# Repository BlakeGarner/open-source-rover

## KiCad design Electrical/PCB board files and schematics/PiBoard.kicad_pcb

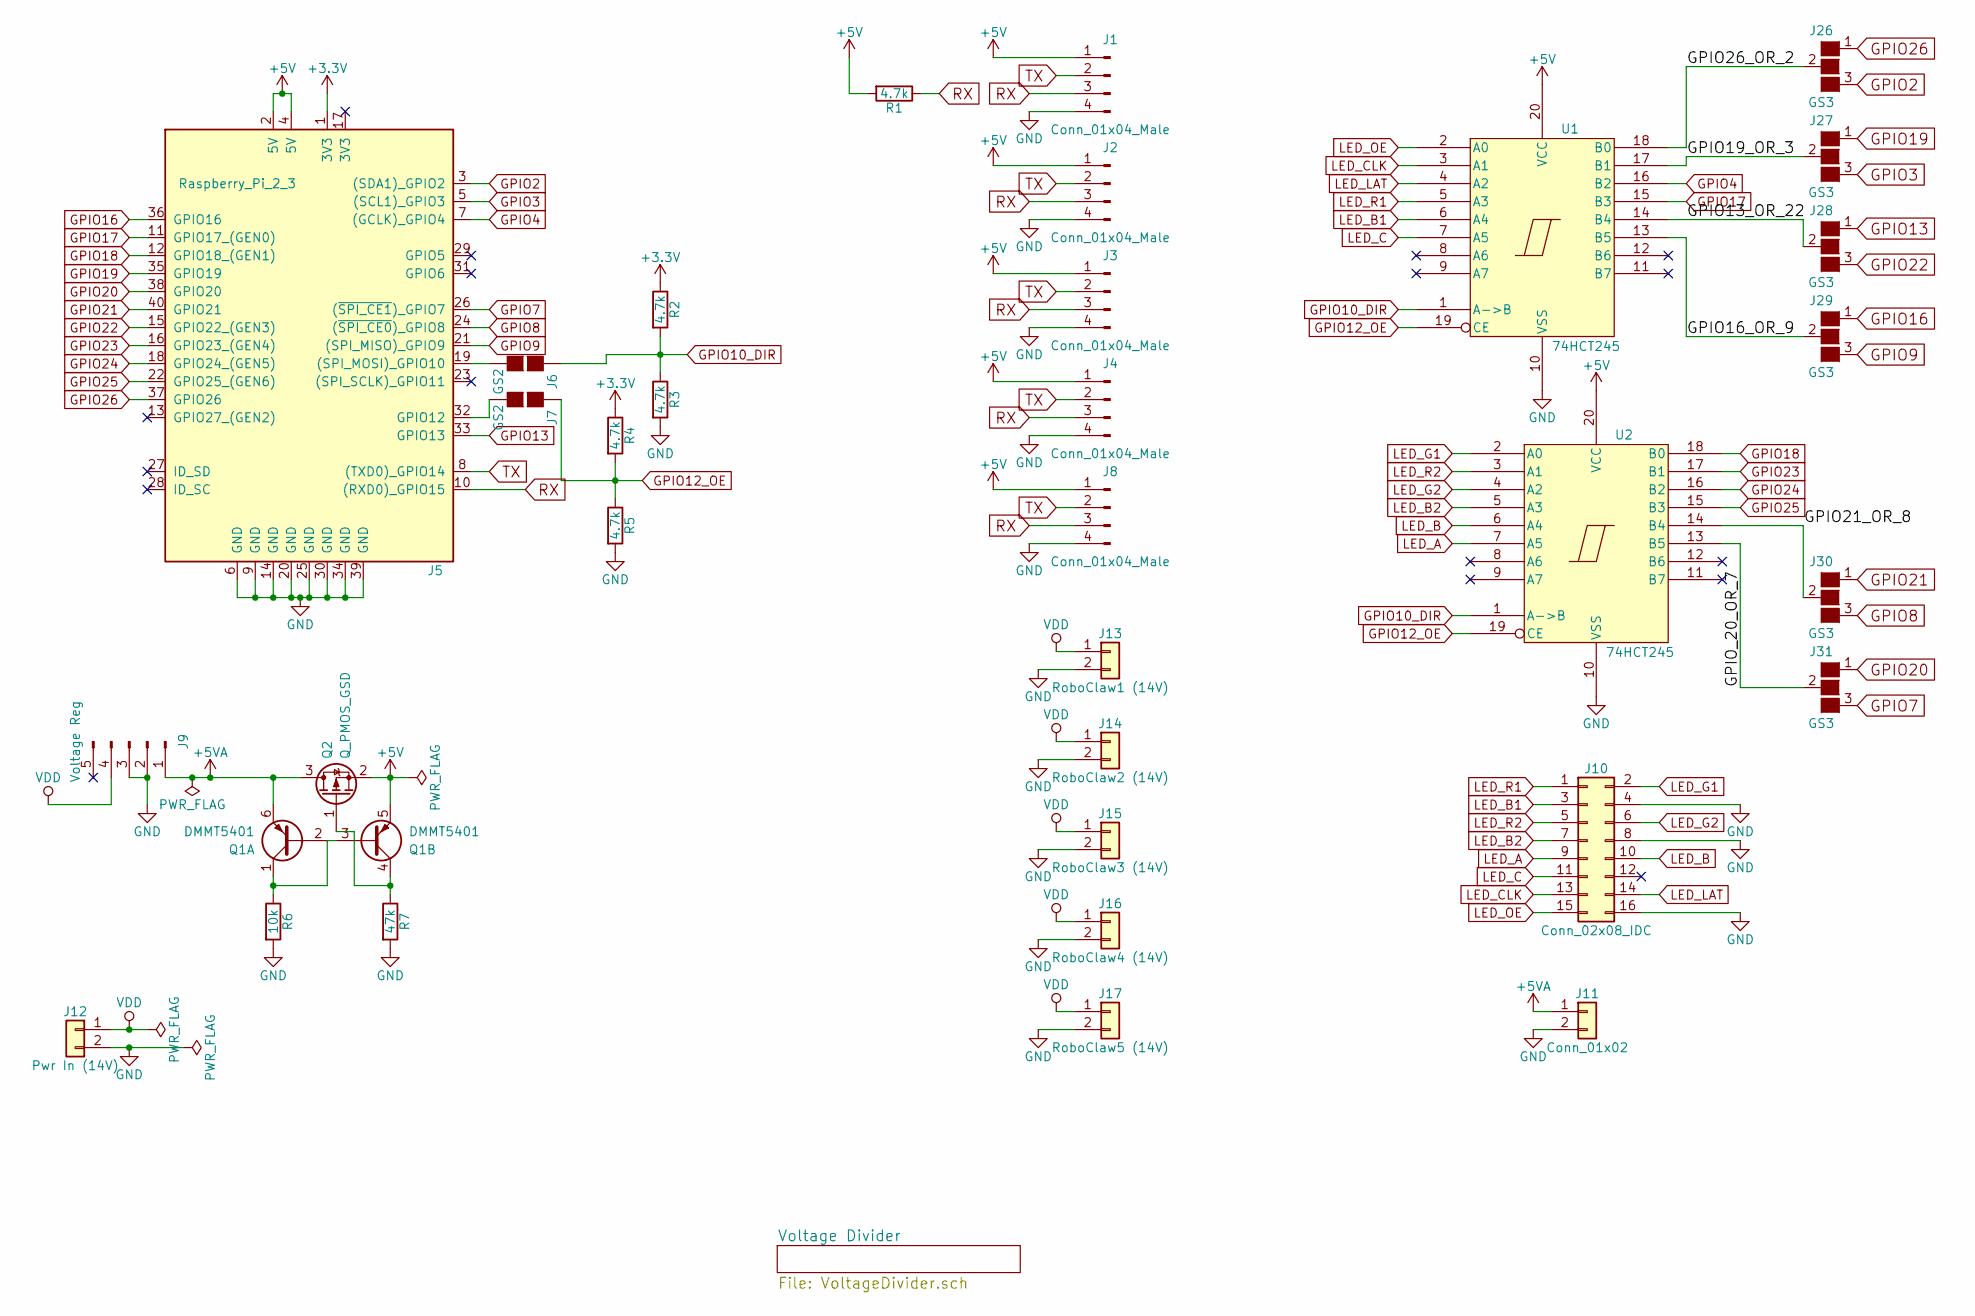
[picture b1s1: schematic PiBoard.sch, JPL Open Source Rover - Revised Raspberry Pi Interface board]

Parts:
J1, J2, J3, J4, J8: Conn_01x04_Male; Pin_Header_Straight_1x04_Pitch2.54mm
J5: Raspberry_Pi_2_3; Socket_Strip_Straight_Raspberry_Pi_2_3
J6, J7: GS2
J9: Voltage Reg; Pin_Header_Straight_1x05_Pitch2.54mm
J10: Conn_02x08_IDC; Multicomp_MC9A12-1634_2x08x2.54mm_Straight
J11: Conn_01x02; PhoenixContact_GMSTBVA-G_02x7.62mm_Vertical
J12: Pwr In (14V); PhoenixContact_GMSTBVA-G_02x7.62mm_Vertical
J13: RoboClaw1 (14V); TerminalBlock_bornier-2_P5.08mm
J14: RoboClaw2 (14V); TerminalBlock_bornier-2_P5.08mm
J15: RoboClaw3 (14V); TerminalBlock_bornier-2_P5.08mm
J16: RoboClaw4 (14V); TerminalBlock_bornier-2_P5.08mm
J17: RoboClaw5 (14V); TerminalBlock_bornier-2_P5.08mm
J26, J27, J28, J29, J30, J31: GS3
Q1: DMMT5401; SOT-23-6; MPN DMMT5401-7-F; Digikey PN DMMT5401-FDICT-ND
Q2: Q_PMOS_GSD; SOT-23; MPN DMG2305UX-13; Digikey PN DMG2305UX-13DICT-ND
R1, R2, R3, R4, R5: 4.7k; R_0805
R6: 10k; R_0805
R7: 47k; R_0805
U1, U2: 74HCT245; TSSOP-20_4.4x6.5mm_Pitch0.65mm

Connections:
+3V3: J5.1 (3V3), R2.1, R4.1
+5V: J1.1, J2.1, J3.1, J4.1, J5.2 (5V), J5.4 (5V), J8.1, Q1.5 (E2), Q2.2 (S), R1.2, U1.20 (VCC), U2.20 (VCC)
+5VA: J9.1, J11.1, Q1.6 (E1), Q2.3 (D)
/GPIO13_OR_22: J28.2 (G2), U1.14 (B4)
/GPIO16_OR_9: J29.2 (G2), U1.13 (B5)
/GPIO19_OR_3: J27.2 (G2), U1.17 (B1)
/GPIO21_OR_8: J30.2 (G2), U2.14 (B4)
/GPIO26_OR_2: J26.2 (G2), U1.18 (B0)
/GPIO_20_OR_7: J31.2 (G2), U2.13 (B5)
GND: J1.4, J2.4, J3.4, J4.4, J5.6 (GND), J5.9 (GND), J5.14 (GND), J5.20 (GND), J5.25 (GND), J5.30 (GND), J5.34 (GND), J5.39 (GND), J8.4, J9.2, J9.3, J10.4, J10.8, J10.16, J11.2, J12.2, J13.2, J14.2, J15.2, J16.2, J17.2, R3.2, R5.2, R6.2, R7.2, U1.10 (VSS), U2.10 (VSS)
GPIO2: J5.3 ((SDA1)_GPIO2), J26.3 (G3)
GPIO3: J5.5 ((SCL1)_GPIO3), J27.3 (G3)
GPIO4: J5.7 ((GCLK)_GPIO4), U1.16 (B2)
GPIO7: J5.26 ((~SPI_CE1~)_GPIO7), J31.3 (G3)
GPIO8: J5.24 ((~SPI_CE0~)_GPIO8), J30.3 (G3)
GPIO9: J5.21 ((SPI_MISO)_GPIO9), J29.3 (G3)
GPIO10_DIR: J6.1 (G1), R2.2, R3.1, U1.1 (A->B), U2.1 (A->B)
GPIO12_OE: J7.1 (G1), R4.2, R5.1, U1.19 (CE), U2.19 (CE)
GPIO13: J5.33 (GPIO13), J28.1 (G1)
GPIO16: J5.36 (GPIO16), J29.1 (G1)
GPIO17: J5.11 (GPIO17_(GEN0)), U1.15 (B3)
GPIO18: J5.12 (GPIO18_(GEN1)), U2.18 (B0)
GPIO19: J5.35 (GPIO19), J27.1 (G1)
GPIO20: J5.38 (GPIO20), J31.1 (G1)
GPIO21: J5.40 (GPIO21), J30.1 (G1)
GPIO22: J5.15 (GPIO22_(GEN3)), J28.3 (G3)
GPIO23: J5.16 (GPIO23_(GEN4)), U2.17 (B1)
GPIO24: J5.18 (GPIO24_(GEN5)), U2.16 (B2)
GPIO25: J5.22 (GPIO25_(GEN6)), U2.15 (B3)
GPIO26: J5.37 (GPIO26), J26.1 (G1)
LED_A: J10.9, U2.7 (A5)
LED_B: J10.10, U2.6 (A4)
LED_B1: J10.3, U1.6 (A4)
LED_B2: J10.7, U2.5 (A3)
LED_C: J10.11, U1.7 (A5)
LED_CLK: J10.13, U1.3 (A1)
LED_G1: J10.2, U2.2 (A0)
LED_G2: J10.6, U2.4 (A2)
LED_LAT: J10.14, U1.4 (A2)
LED_OE: J10.15, U1.2 (A0)
LED_R1: J10.1, U1.5 (A3)
LED_R2: J10.5, U2.3 (A1)
unnamed: J5.19 ((SPI_MOSI)_GPIO10), J6.2 (G2)
unnamed: J5.32 (GPIO12), J7.2 (G2)
unnamed: Q1.1 (C1), Q1.2 (B1), Q1.3 (B2), R6.1
unnamed: Q1.4 (C2), Q2.1 (G), R7.1
RX: J1.3, J2.3, J3.3, J4.3, J5.10 ((RXD0)_GPIO15), J8.3, R1.1
TX: J1.2, J2.2, J3.2, J4.2, J5.8 ((TXD0)_GPIO14), J8.2
VDD: J9.4, J12.1, J13.1, J14.1, J15.1, J16.1, J17.1

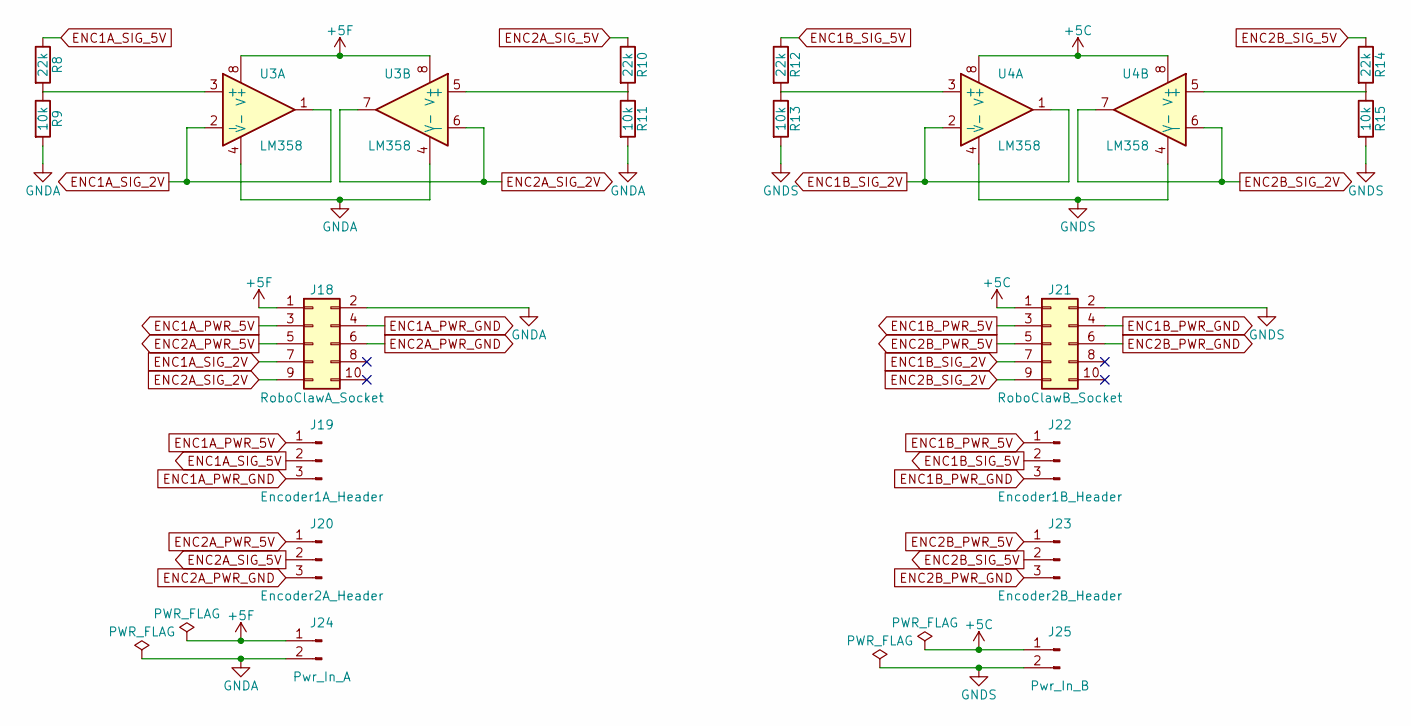
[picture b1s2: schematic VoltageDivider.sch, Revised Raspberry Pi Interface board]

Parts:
J18: RoboClawA_Socket; Pin_Header_Straight_2x05_Pitch2.54mm
J19: Encoder1A_Header; Pin_Header_Straight_1x03_Pitch2.54mm
J20: Encoder2A_Header; Pin_Header_Straight_1x03_Pitch2.54mm
J21: RoboClawB_Socket; Pin_Header_Straight_2x05_Pitch2.54mm
J22: Encoder1B_Header; Pin_Header_Straight_1x03_Pitch2.54mm
J23: Encoder2B_Header; Pin_Header_Straight_1x03_Pitch2.54mm
J24: Pwr_In_A; Pin_Header_Straight_2x01_Pitch2.54mm
J25: Pwr_In_B; Pin_Header_Straight_2x01_Pitch2.54mm
R8, R10, R12, R14: 22k; R_0805
R9, R11, R13, R15: 10k; R_0805
U3: LM358; SOIC-8_3.9x4.9mm_Pitch1.27mm
U4: LM358; SOIC-8_3.9x4.9mm_Pitch1.27mm; MPN LM358DR; Digikey PN 296-1014-1-ND

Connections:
+5C: J21.1, J25.1, U4.8 (V+)
+5F: J18.1, J24.1, U3.8 (V+)
ENC1A_PWR_5V: J18.3, J19.1
ENC1A_PWR_GND: J18.4, J19.3
ENC1A_SIG_2V: J18.7, U3.1, U3.2 (-)
ENC1A_SIG_5V: J19.2, R8.1
ENC1B_PWR_5V: J21.3, J22.1
ENC1B_PWR_GND: J21.4, J22.3
ENC1B_SIG_2V: J21.7, U4.1, U4.2 (-)
ENC1B_SIG_5V: J22.2, R12.1
ENC2A_PWR_5V: J18.5, J20.1
ENC2A_PWR_GND: J18.6, J20.3
ENC2A_SIG_2V: J18.9, U3.6 (-), U3.7
ENC2A_SIG_5V: J20.2, R10.1
ENC2B_PWR_5V: J21.5, J23.1
ENC2B_PWR_GND: J21.6, J23.3
ENC2B_SIG_2V: J21.9, U4.6 (-), U4.7
ENC2B_SIG_5V: J23.2, R14.1
GNDA: J18.2, J24.2, R9.2, R11.2, U3.4 (V-)
GNDS: J21.2, J25.2, R13.2, R15.2, U4.4 (V-)
unnamed: R8.2, R9.1, U3.3 (+)
unnamed: R10.2, R11.1, U3.5 (+)
unnamed: R12.2, R13.1, U4.3 (+)
unnamed: R14.2, R15.1, U4.5 (+)

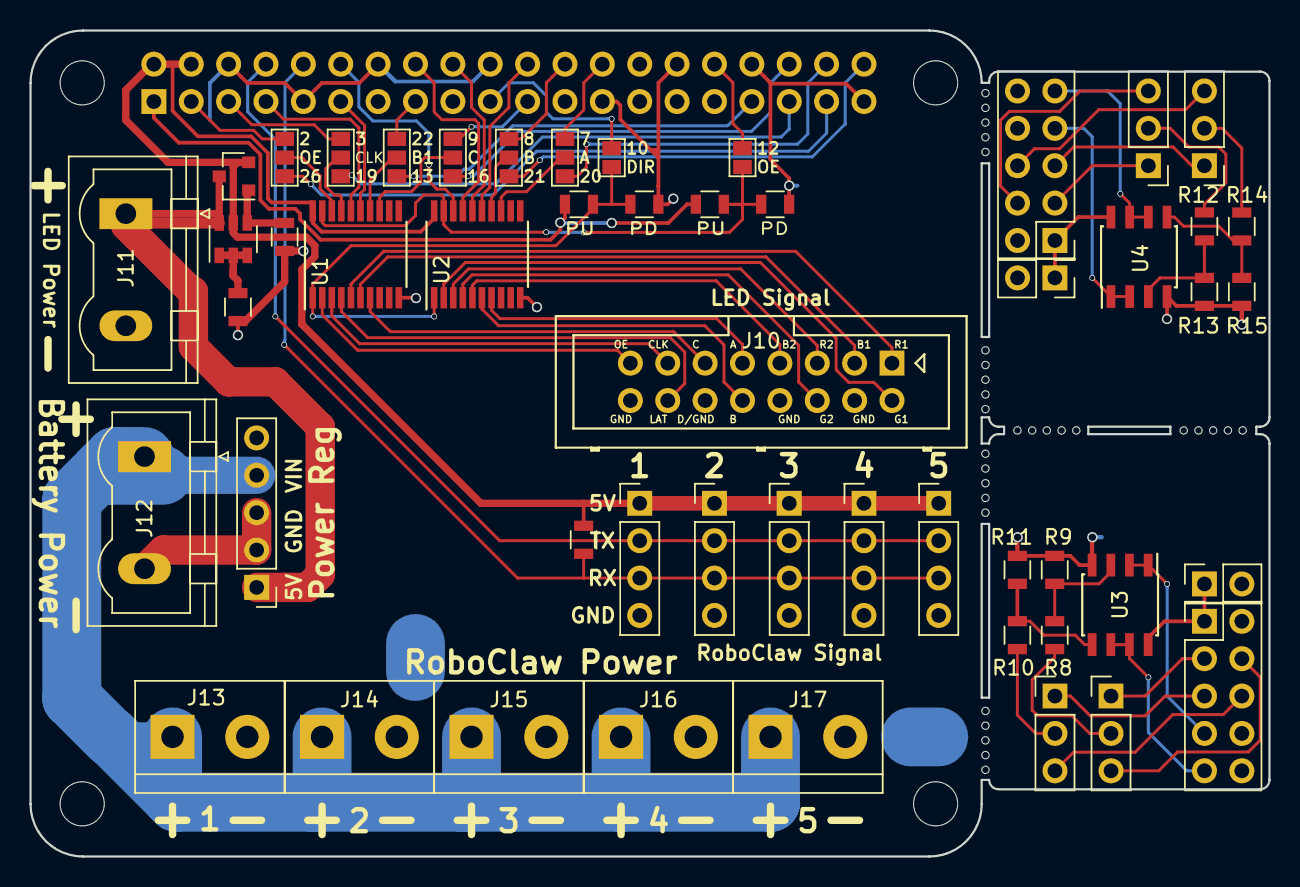
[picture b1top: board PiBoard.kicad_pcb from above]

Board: 2 copper layers, 84.2 x 56.1 mm, 52 parts (1 on the bottom side), 73 nets.

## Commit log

2018-08-27 Final copy of PCB rework
2018-08-27 Switched submodule to local fork
2019-05-26 Added final notes post install.
